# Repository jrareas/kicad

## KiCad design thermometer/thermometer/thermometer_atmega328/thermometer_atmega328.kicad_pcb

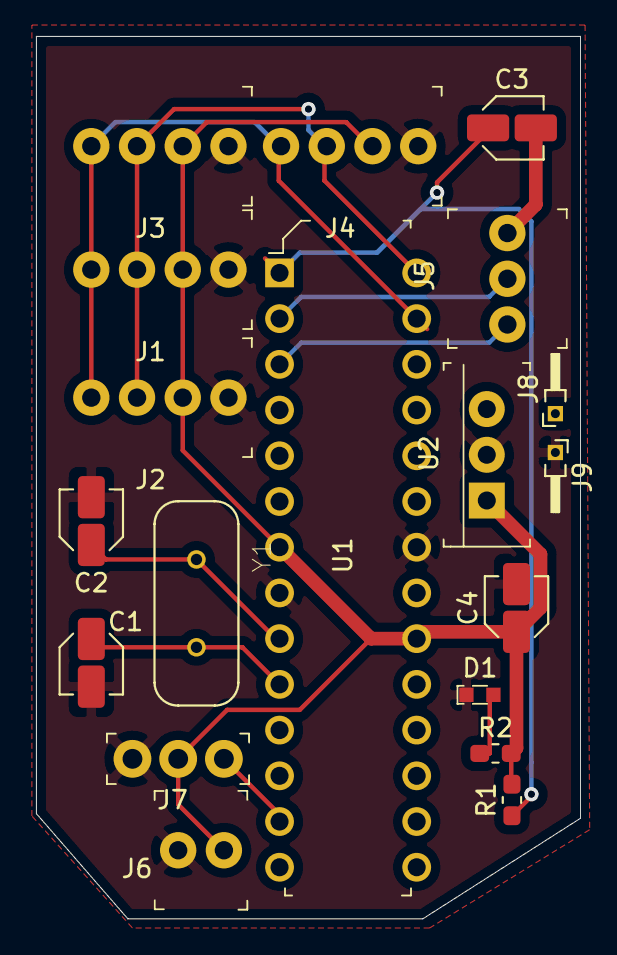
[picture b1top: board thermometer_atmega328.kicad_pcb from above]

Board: 2 copper layers, 30.2 x 49.0 mm, 19 parts (0 on the bottom side), 13 nets.

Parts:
C1: 22pf; C_Elec_3x5.4
C2: 22; C_Elec_3x5.4
C3: 104; C_Elec_3x5.4
C4: 10k; C_Elec_3x5.4
D1: LED; LED_2-SMD_No_Lead_1.7x0.8mm
J1, J2, J3, J4: 0022232041; PinHeader_1x4_P2.54mm_Drill1.02mm
J5: 640456-3; PinHeader_1x3_P2.54mm_Drill1.02mm
J6: 22-23-2021; PinHeader_1x2_P2.54mm_Drill1.02mm
J7: 640456-3; PinHeader_1x3_P2.54_Drill1.1mm
J8, J9: Conn_01x01_Female; PinHeader_1x01_P1.00mm_Horizontal
R1, R2: 220; R_0603_1608Metric_Pad1.05x0.95mm_HandSolder
U1: ATMEGA328-PU; DIP-28_W7.62mm
U2: L4931CZ50-AP; TO-220-3
Y1: 16.0000MHz; XTAL_ECS-160-18-4XEN

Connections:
GND: C1.2, C2.2, C4.2, D1.1, J1.1, J2.1, J3.1, J4.1, J6.2, J7.3, J9.1, U1.8, U1.22, U2.2
unnamed: C1.1, U1.10, Y1.2
unnamed: C2.1, U1.9, Y1.1
unnamed: C3.1, R1.1, U1.1
unnamed: C3.2, J5.3
unnamed: C4.1, J1.2, J2.2, J3.2, J4.2, J6.1, J7.2, R1.2, R2.2, U1.7, U1.20, U2.1
unnamed: D1.2, R2.1
unnamed: J1.3, J2.3, J3.3, J4.3, U1.28
unnamed: J1.4, J2.4, J3.4, J4.4, U1.27
unnamed: J5.1, U1.3
unnamed: J5.2, U1.2
unnamed: J7.1, U1.13
VCC: J8.1, U2.3
